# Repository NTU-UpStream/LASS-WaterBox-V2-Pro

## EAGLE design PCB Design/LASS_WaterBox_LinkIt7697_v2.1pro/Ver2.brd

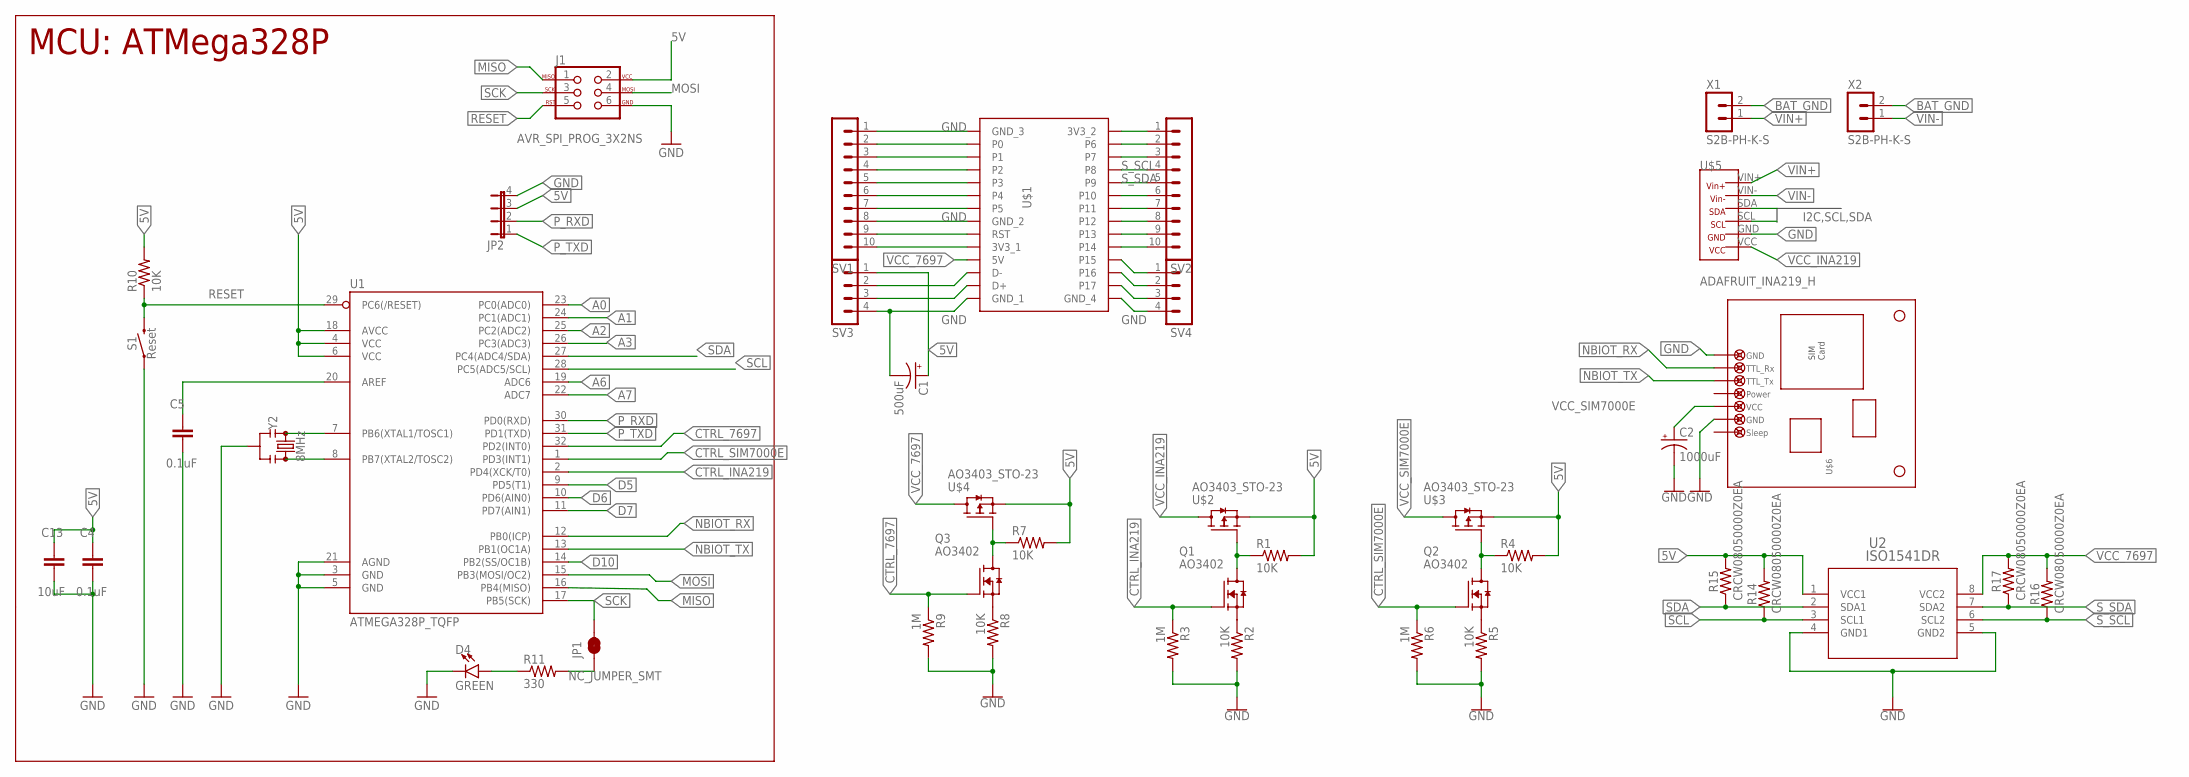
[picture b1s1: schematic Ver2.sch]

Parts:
C1: 500uF; TT2D5
C2: 1000uF; TT2D5L
C4, C5: 0.1uF; CAP_0805
C13: 10uF; CAP_0805
D4: GREEN; LED-0603
J1: AVR_SPI_PROG_3X2NS; 2X3-NS
JP1: NC_JUMPER_SMT; SMT-JUMPER_2_NC_TRACE_SILK
JP2: JP4E; JP4
Q1, Q2, Q3: AO3402; SOT95P280X125-3N
R1, R2, R4, R5, R7, R8, R10: 10K; RES_0805
R3, R6, R9: 1M; RES_0805
R11: 330; RES_0805
R14, R15, R16, R17: CRCW08050000Z0EA; RES_0805
S1: Reset; TACTILE_SWITCH_SMD_4.5MM
SV1, SV2: MA10-1
SV3, SV4: MA04-1
U1: ATMEGA328P_TQFP; TQFP32-08
U2: ISO1541DR; D8
U$1: LINKIT_7697
U$2, U$3, U$4: AO3403_STO-23; SOT23
U$5: ADAFRUIT_INA219_H
U$6: SIM7000E; SIM7000E_AND-GLOBAL
X1, X2: S2B-PH-K-S
Y2: 8MHz; RESONATOR-SMD-3.2X1.3

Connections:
5V: C1.+, C4.1, C13.1, J1.2, JP2.3, R1.2, R4.2, R7.2, R10.2, R14.2, R15.2, SV3.1, U1.4 (VCC), U1.6 (VCC), U1.18 (AVCC), U2.1 (VCC1), U$2.2 (S), U$3.2 (S), U$4.2 (S)
A0: U1.23 (PC0(ADC0))
A1: U1.24 (PC1(ADC1))
A2: U1.25 (PC2(ADC2))
A3: U1.26 (PC3(ADC3))
A6: U1.19 (ADC6)
A7: U1.22 (ADC7)
BAT_GND: X1.2, X2.2
CTRL_7697: Q3.1 (G), R9.1, U1.32 (PD2(INT0))
CTRL_INA219: Q1.1 (G), R3.1, U1.2 (PD4(XCK/T0))
CTRL_SIM7000E: Q2.1 (G), R6.1, U1.1 (PD3(INT1))
D5: U1.9 (PD5(T1))
D6: U1.10 (PD6(AIN0))
D7: U1.11 (PD7(AIN1))
D10: U1.14 (PB2(SS/OC1B))
GND: C1.-, C2.-, C4.2, C5.2, C13.2, D4.C, J1.6, JP2.4, R2.2, R3.2, R5.2, R6.2, R8.2, R9.2, S1.2 (1), S1.3 (1), SV1.1, SV1.8, SV3.4, SV4.4, U1.3 (GND), U1.5 (GND), U1.21 (AGND), U2.4 (GND1), U2.5 (GND2), U$1.GND_1, U$1.GND_2, U$1.GND_3, U$1.GND_4, U$5.GND, U$6.S_GND, U$6.V_GND, Y2.2
MISO: J1.1, U1.16 (PB4(MISO))
MOSI: J1.4, U1.15 (PB3(MOSI/OC2))
unnamed: Q1.2 (S), R2.1
unnamed: Q1.3 (D), R1.1, U$2.1 (G)
unnamed: Q2.2 (S), R5.1
unnamed: Q2.3 (D), R4.1, U$3.1 (G)
unnamed: Q3.2 (S), R8.1
unnamed: Q3.3 (D), R7.1, U$4.1 (G)
unnamed: U1.7 (PB6(XTAL1/TOSC1)), Y2.1
unnamed: SV1.2, U$1.P0
unnamed: SV1.3, U$1.P1
unnamed: SV1.4, U$1.P2
unnamed: SV1.5, U$1.P3
unnamed: SV1.6, U$1.P4
unnamed: SV1.7, U$1.P5
unnamed: U1.8 (PB7(XTAL2/TOSC2)), Y2.3
unnamed: SV1.9, U$1.RST
unnamed: SV1.10, U$1.3V3_1
unnamed: SV3.2, U$1.D-
unnamed: SV3.3, U$1.D+
unnamed: C5.1, U1.20 (AREF)
unnamed: JP1.1, R11.2
unnamed: SV4.3, U$1.P17
unnamed: SV4.2, U$1.P16
unnamed: SV4.1, U$1.P15
unnamed: SV2.10, U$1.P14
unnamed: SV2.9, U$1.P13
unnamed: SV2.8, U$1.P12
unnamed: SV2.7, U$1.P11
unnamed: SV2.6, U$1.P10
unnamed: D4.A, R11.1
unnamed: SV2.3, U$1.P7
unnamed: SV2.2, U$1.P6
unnamed: SV2.1, U$1.3V3_2
NBIOT_RX: U1.12 (PB0(ICP)), U$6.RX
NBIOT_TX: U1.13 (PB1(OC1A)), U$6.TX
P_RXD: JP2.2, U1.30 (PD0(RXD))
P_TXD: JP2.1, U1.31 (PD1(TXD))
RESET: J1.5, R10.1, S1.1 (2), S1.4 (2), U1.29 (PC6(/RESET))
SCK: J1.3, JP1.2, U1.17 (PB5(SCK))
SCL: R14.1, U1.28 (PC5(ADC5/SCL)), U2.3 (SCL1), U$5.SCL
SDA: R15.1, U1.27 (PC4(ADC4/SDA)), U2.2 (SDA1), U$5.SDA
S_SCL: R16.1, SV2.4, U2.6 (SCL2), U$1.P8
S_SDA: R17.1, SV2.5, U2.7 (SDA2), U$1.P9
VCC_7697: R16.2, R17.2, U2.8 (VCC2), U$1.5V, U$4.3 (D)
VCC_INA219: U$2.3 (D), U$5.VCC
VCC_SIM7000E: C2.+, U$3.3 (D), U$6.VCC
VIN+: U$5.VIN+, X1.1
VIN-: U$5.VIN-, X2.1

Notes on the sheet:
MCU: ATMega328P

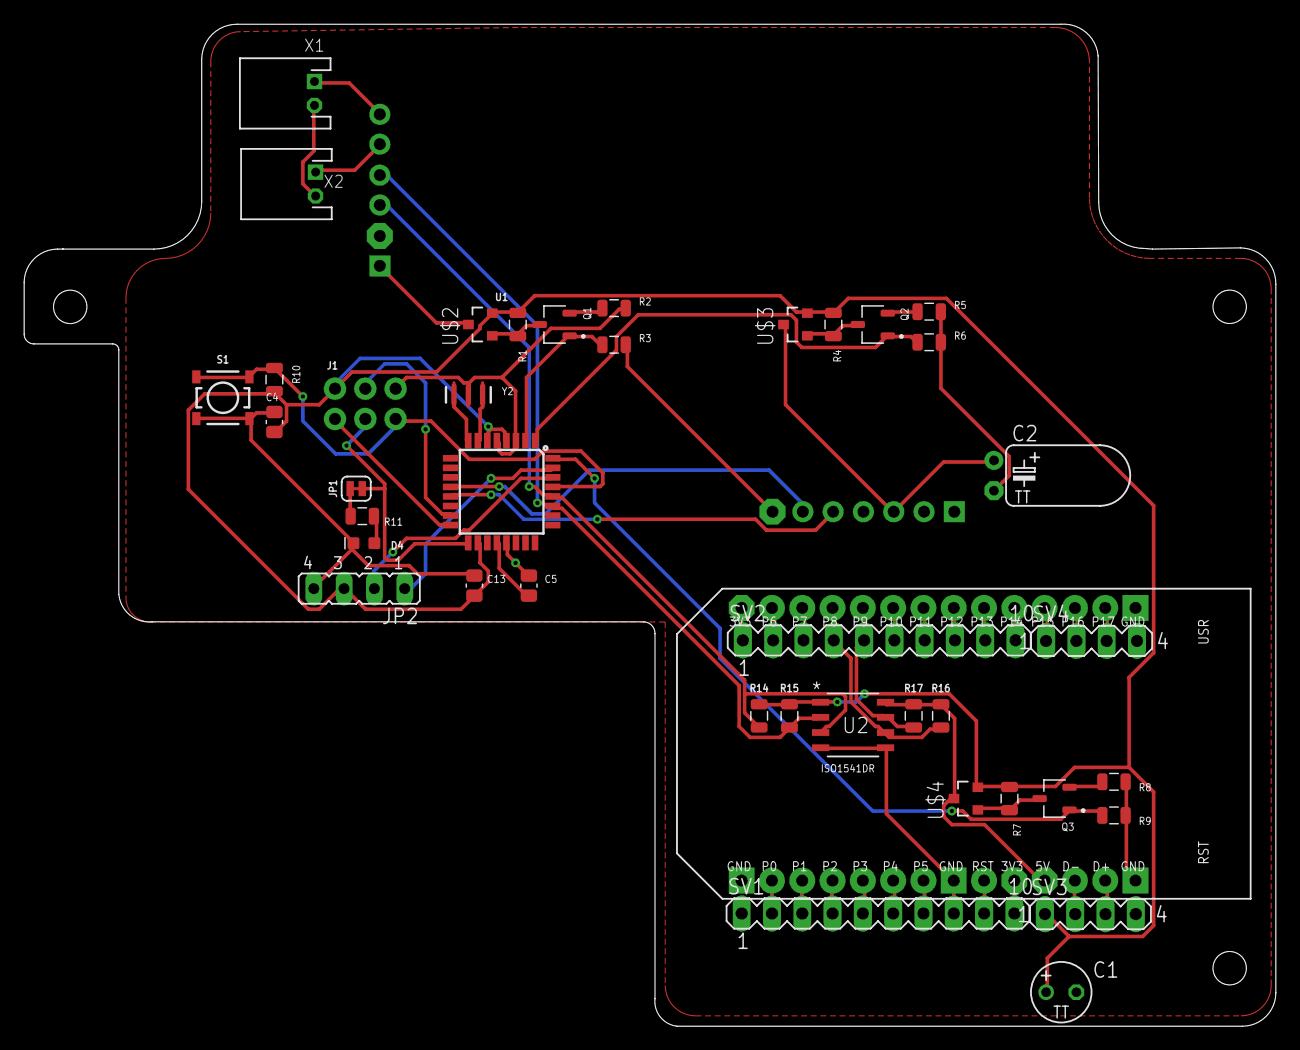
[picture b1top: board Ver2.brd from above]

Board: 2 copper layers, 104.9 x 84.0 mm, 43 parts (1 on the bottom side), 55 nets.

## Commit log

2022-01-22 Ver 1.0
2022-01-22 Ver 1.0
    Modify PMU_GPIO_Control.ino File Name
2022-01-22 Ver 1.1
    add pcb file
2022-01-22 Ver 1.1
    modify LED function
2022-01-22 remove .DS_Store
2022-02-16 modify ??
2022-02-16 modify ArduinoLibrary
2022-03-02 Ver 1.0
    add MQTT package
2022-03-08 update TestCode
    update TestCode
2022-03-10 add PMU V2.0
    add PMU V2.0
2022-03-10 Add menu system
2022-03-10 Add menusystem library
2022-03-10 modify
2022-03-10 add sim7000G TCP command
2022-03-10 Add all ezo library
2022-03-10 update AllSystem MCU V2.1
    update AllSystem MCU V2.1
2022-04-25 test
2022-05-08 Modify the number of digits at PMU data
2022-05-08 fixed MenuSystem.cpp error
    function: int MenuSystem::SPI_select(SPI_device device)
    add return 0;
2022-05-08 add MCU test Code: PMU CMD
2022-05-09 upload sdcard config file
2022-05-09 add SIMCOM function
2022-05-09 fixed AllSystem_PMU_V2.1.b.ino connect package formate
2022-05-09 modify TCP Connect waiting time
2022-05-20 Ver 2.1.b
2022-05-20 fix INA219 Power On timing bug
2022-05-20 recover ads1x15 library
2022-05-20 add .gitignore
2022-06-03 modify Turbidity ADC formula
2022-06-03 Correct Interval
2022-06-03 Change NTU to mV
2022-06-28 update LASS Format
2022-06-28 update WaterBox_PMU.cpp Note
2022-06-29 fixed auto add Field data
2022-08-30 change development environment
2022-10-12 modify code with nothing
2022-10-12 init ublox library Ver 0.1
2022-10-24 Ver 1.0
    add Power control pin
    add MQTT init function
    add MQTT publish function
2022-10-24 modify function, ublox::ON(float _sec)
2022-10-24 init Ver 0.1
2023-02-05 Improve upload process
2023-02-05 Ver 0.5
    ublox.h unit test done
2023-02-06 modify process
2023-02-28 modify comment
2023-02-28 reduce dynamic memory size
2023-03-21 modify string
    String -> char array
2023-03-25 fixed TestCode_MCU I2C clock setting
2023-03-25 fixed bug WaterBox_PMU.cpp
2023-03-28 Simplify program code
2023-03-29 init All System PMU V2.3
2023-03-29 modify debug formate
2023-03-29 Ver 1.1
2023-03-29 rename file name: AllSystem_PMU_V2.3_ublox
2023-03-30 modify comment c
2023-04-01 init UK NBIOT Test
2023-04-12 [BUG Fixed] NBIOT Power OFF
2023-04-12 [BUG Fixed] Test
2023-04-13 fixed (uint8_t->uint_16_t) _PowerSave memory overflow
2023-04-13 Fixed _SleepSec overwrite by _PowerSave

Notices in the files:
parts and their libraries:
SparkFun-Clocks: Licensing: Creative Commons ShareAlike 4.0 International - https://creativecommons.org/licenses/by-sa/4.0
